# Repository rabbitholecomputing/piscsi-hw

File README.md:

# Zulu control board hardware
## zulu-ctrl-board-v1.0-kicad
OLED with rotatory with a push button and two more buttons
with an I2C and an added interrupt line.

derived from "ctrl_board_v1p6" in this project:
https://github.com/PiSCSI/piscsi-hw

# piscsi-hw
Hardware Repository for PiSCSI

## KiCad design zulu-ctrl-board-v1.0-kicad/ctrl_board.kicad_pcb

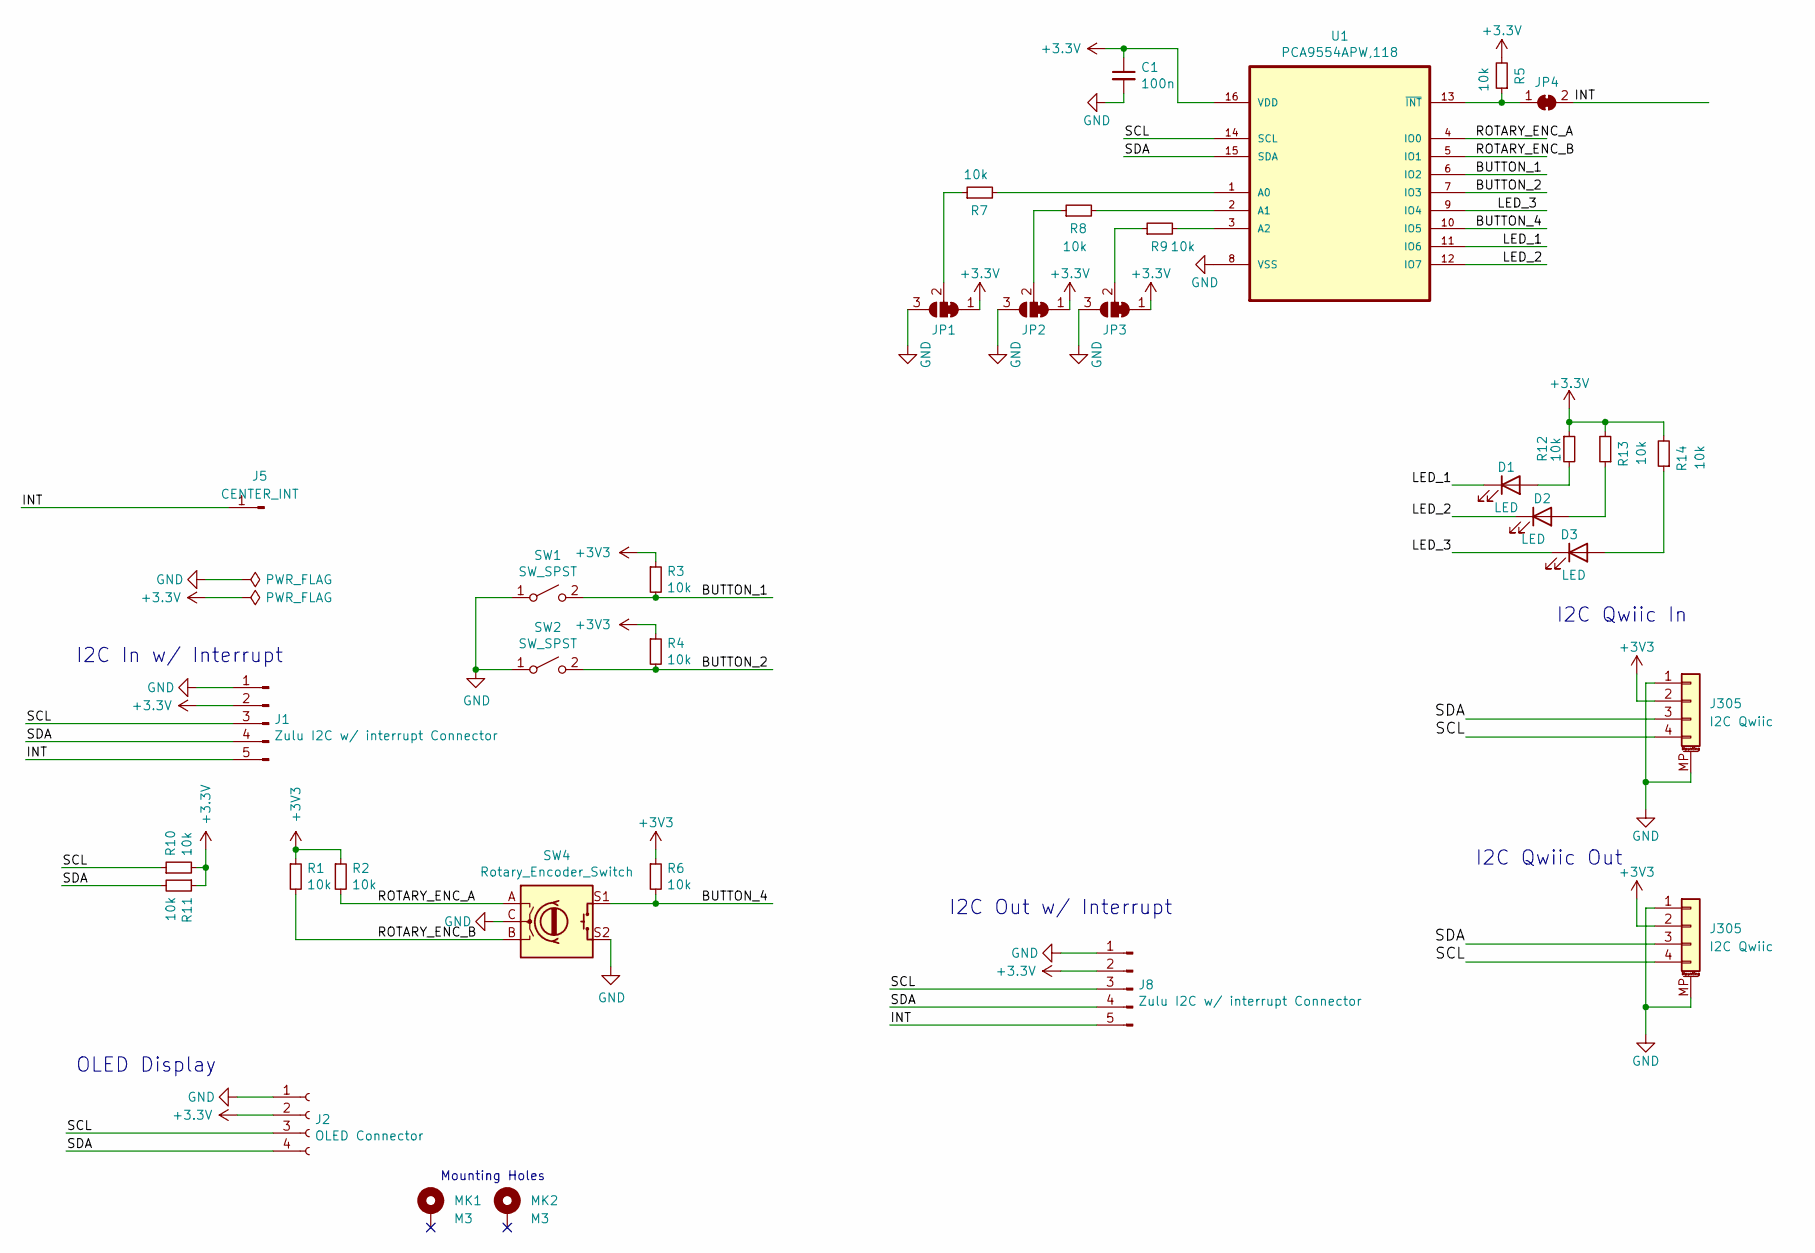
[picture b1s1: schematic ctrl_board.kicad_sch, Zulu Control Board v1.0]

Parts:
C1: 100n; C_0805_2012Metric; LCSC C49678
D1, D2, D3: LED; LED_D5.0mm
J1, J8: Zulu I2C w/ interrupt Connector; PinHeader_1x05_P2.54mm_Vertical
J2: OLED Connector; 0.9_and_1.3_in_OLED_Footprint
J5: CENTER_INT; PinHeader_1x01_P2.54mm_Vertical
J305: I2C Qwiic; JST_SH_SM04B-SRSS-TB_1x04-1MP_P1.00mm_Horizontal; LCSC N/A
JP1, JP2, JP3: SolderJumper_3_Bridged12; SolderJumper-3_P1.3mm_Bridged12_RoundedPad1.0x1.5mm
JP4: SolderJumper_2_Open; SolderJumper-2_P1.3mm_Bridged_RoundedPad1.0x1.5mm
MK1, MK2: M3; MountingHole_3.2mm_M3_Pad
R1, R2, R3, R4, R5, R6, R7, R8, R9, R10, R11, R12, R13, R14: 10k; R_0805_2012Metric; LCSC C17414
SW1, SW2: SW_SPST; SW_PUSH_6mm_H5mm; LCSC C110153
SW4: Rotary_Encoder_Switch; RotaryEncoder_Alps_EC11E-Switch_Vertical_H20mm
U1: PCA9554APW,118; TSSOP-16_4.4x5mm_P0.65mm; MPN PCA9554APW,118; LCSC C86803

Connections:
/BUTTON_1: R3.2, SW1.2 (B), U1.6 (IO2)
/BUTTON_2: R4.2, SW2.2 (B), U1.7 (IO3)
/BUTTON_4: R6.2, SW4.S1, U1.10 (IO5)
/INT: J1.5, J5.1, J8.5, JP4.2 (B)
/LED_1: D1.1 (K), U1.11 (IO6)
/LED_2: D2.1 (K), U1.12 (IO7)
/LED_3: D3.1 (K), U1.9 (IO4)
/ROTARY_ENC_A: R2.2, SW4.A, U1.4 (IO0)
/ROTARY_ENC_B: R1.2, SW4.B, U1.5 (IO1)
/SCL: J1.3, J2.3, J8.3, R10.1, U1.14 (SCL); also elsewhere on the board
/SDA: J1.4, J2.4, J8.4, R11.2, U1.15 (SDA); also elsewhere on the board
GND: C1.2, J1.1, J2.1, J8.1, JP1.3 (B), JP2.3 (B), JP3.3 (B), SW1.1 (A), SW2.1 (A), SW4.C, SW4.S2, U1.8 (VSS); also elsewhere on the board
unnamed: D1.2 (A), R12.2
unnamed: D2.2 (A), R13.1
unnamed: D3.2 (A), R14.1
unnamed: JP1.2 (C), R7.1
unnamed: JP2.2 (C), R8.1
unnamed: JP3.2 (C), R9.1
unnamed: JP4.1 (A), R5.1, U1.13 (~INT)
unnamed: R7.2, U1.1 (A0)
unnamed: R8.2, U1.2 (A1)
unnamed: R9.2, U1.3 (A2)

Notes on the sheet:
I2C Out w/ Interrupt
I2C Qwiic In
I2C Qwiic Out
OLED Display
Mounting Holes
I2C In w/ Interrupt

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
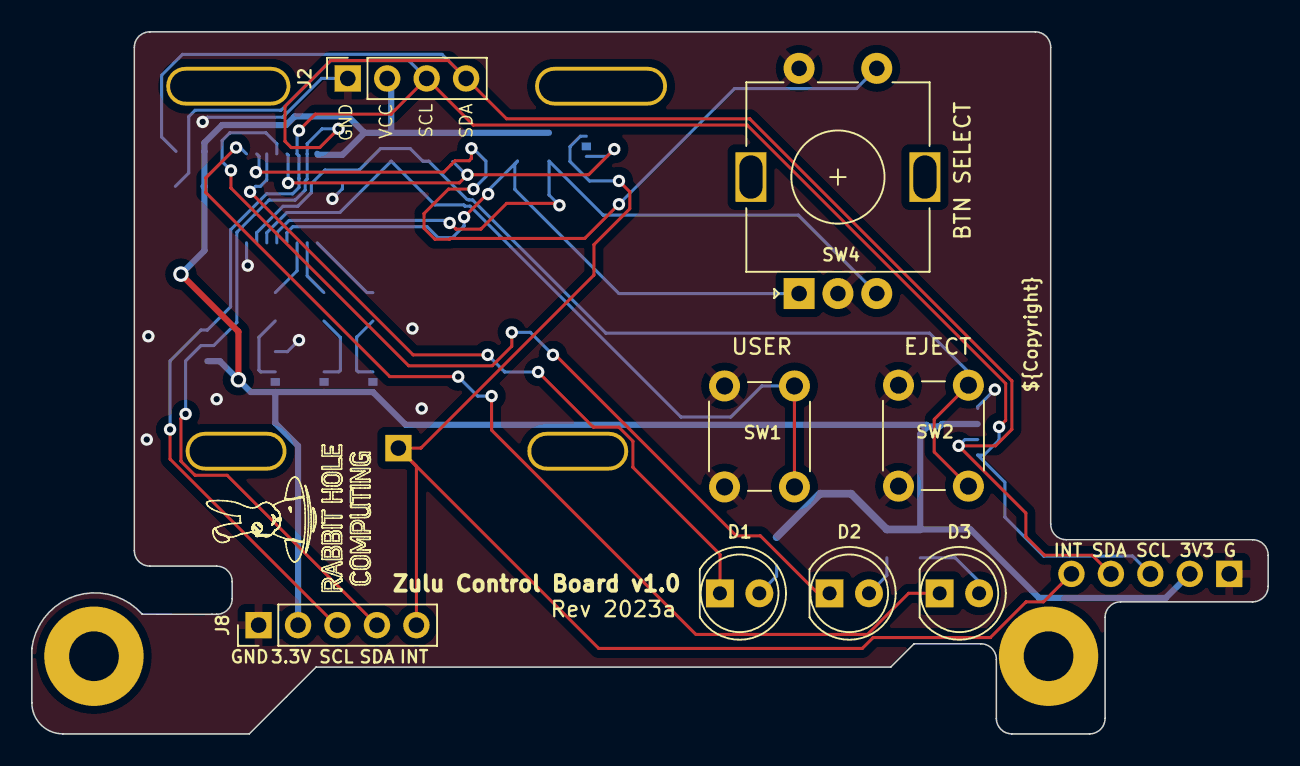
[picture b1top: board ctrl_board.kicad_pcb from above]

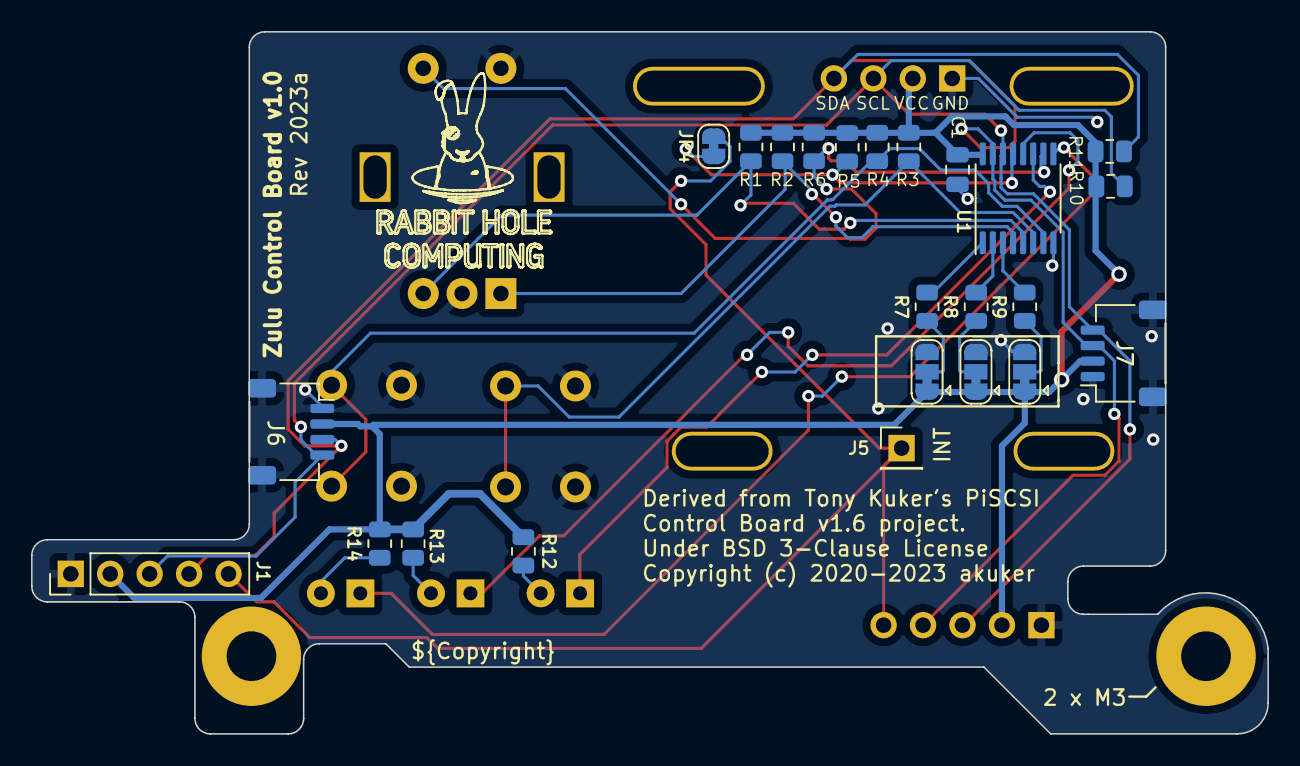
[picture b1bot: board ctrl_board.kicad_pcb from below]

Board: 2 copper layers, 79.6 x 45.2 mm, 34 parts (26 on the bottom side), 23 nets.

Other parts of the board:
J6, J7: I2C Qwiic; JST_SH_SM04B-SRSS-TB_1x04-1MP_P1.00mm_Horizontal

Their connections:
/SCL: J6.4, J7.4; also elsewhere on the board
/SDA: J6.3, J7.3; also elsewhere on the board
GND: J6.1, J6.MP (MountPin), J7.1, J7.MP (MountPin); also elsewhere on the board

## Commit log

2023-08-17 Rough board out line done
    This should fit the two target compact boards.
2023-08-17 Layout done for the Zulu Control Board v1.0
    Layout done for revision 2023a.
2023-08-17 JLCPCB fixes
    Fixed rotation of GPIO expansion IC.
    Modified GitHub workflow
2023-08-17 Fix workflow path typo
    Fixed GitHub workflow image upload source file path.

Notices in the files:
zulu-ctrl-board-v1.0-kicad/ctrl_board.kicad_pcb:
Under BSD 3-Clause License
Copyright (c) 2020-2023 akuker
parts and their libraries:
Copyright: © 2023 Rabbit Hole Computing LLC
